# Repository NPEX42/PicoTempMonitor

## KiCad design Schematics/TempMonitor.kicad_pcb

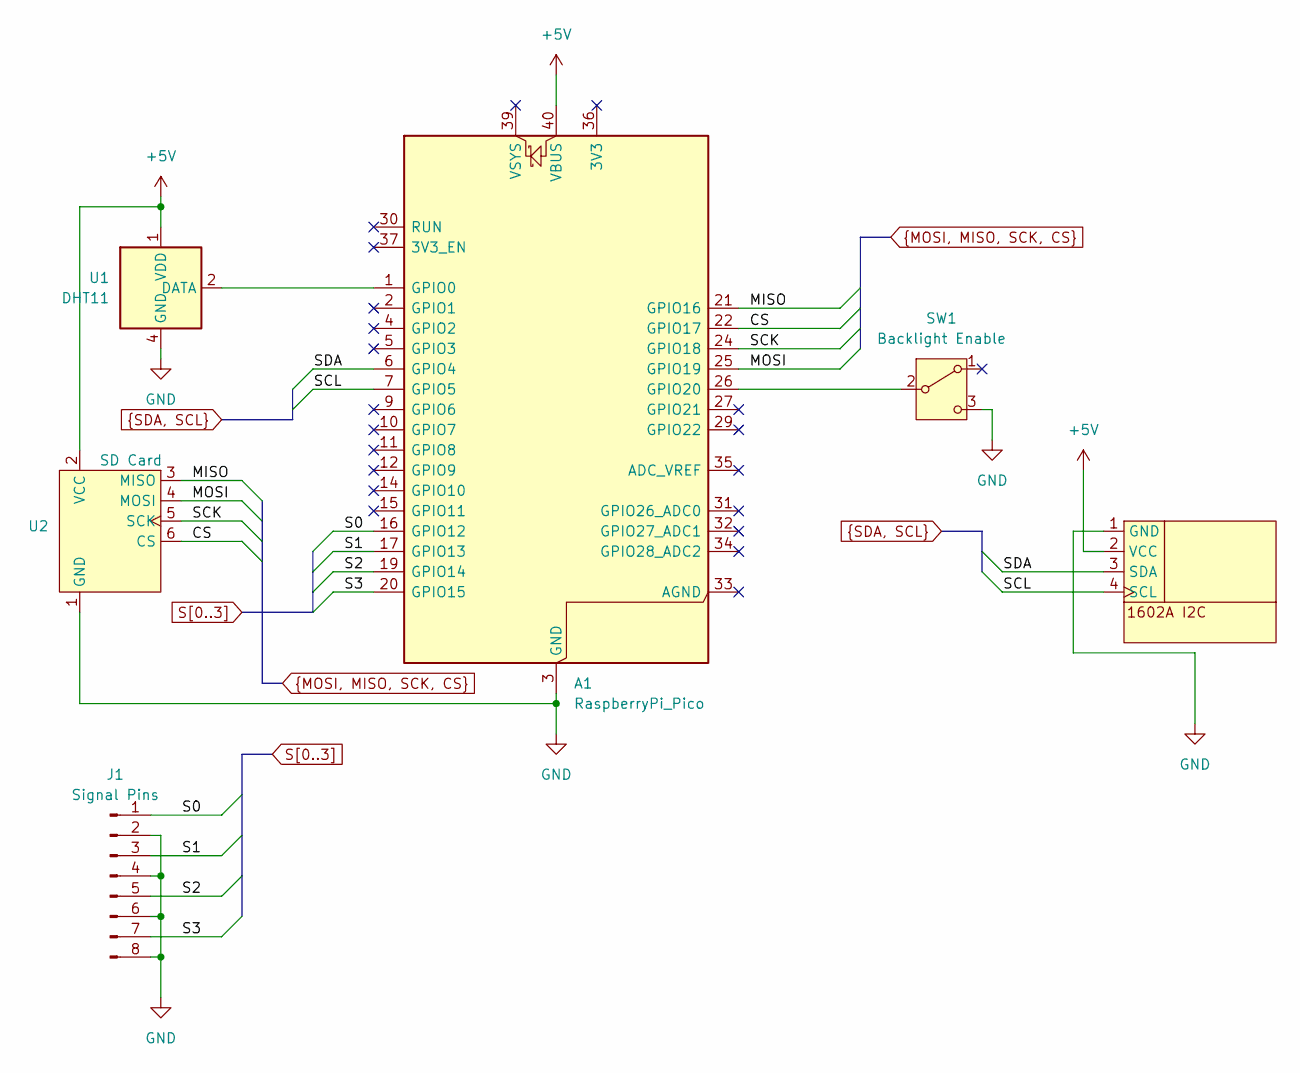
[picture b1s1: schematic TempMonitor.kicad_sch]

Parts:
A1: RaspberryPi_Pico; RaspberryPi_Pico_Common_THT
J1: Signal Pins; PinHeader_1x08_P2.54mm_Vertical
SW1: Backlight Enable; PinHeader_1x03_P2.54mm_Vertical
U1: DHT11; Aosong_DHT11_5.5x12.0_P2.54mm
U2: SD Card; PinHeader_1x06_P2.54mm_Vertical
U3: I2C LCD

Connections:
+5V: A1.40 (VBUS), U1.1 (VDD), U2.2 (VCC), U3.2 (VCC)
CS: A1.22 (GPIO17), U2.6 (CS)
GND: A1.3 (GND), A1.8 (GND), A1.13 (GND), A1.18 (GND), A1.23 (GND), A1.28 (GND), A1.38 (GND), J1.2, J1.4, J1.6, J1.8, SW1.3 (C), U1.4 (GND), U2.1 (GND), U3.1 (GND)
MISO: A1.21 (GPIO16), U2.3 (MISO)
MOSI: A1.25 (GPIO19), U2.4 (MOSI)
unnamed: A1.1 (GPIO0), U1.2 (DATA)
unnamed: A1.26 (GPIO20), SW1.2 (B)
S0: A1.16 (GPIO12), J1.1
S1: A1.17 (GPIO13), J1.3
S2: A1.19 (GPIO14), J1.5
S3: A1.20 (GPIO15), J1.7
SCK: A1.24 (GPIO18), U2.5 (SCK)
SCL: A1.7 (GPIO5), U3.4 (SCL)
SDA: A1.6 (GPIO4), U3.3 (SDA)

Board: 2 copper layers, 6 parts (0 on the bottom side), 14 nets, no tracks yet.

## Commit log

2025-04-16 Added LCD Libs
2025-04-16 Added KiCAD Project Files
